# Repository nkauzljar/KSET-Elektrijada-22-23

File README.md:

# KSET-Elektrijada-22-23
KiCad project for KSET Elektrijada 2022/2023

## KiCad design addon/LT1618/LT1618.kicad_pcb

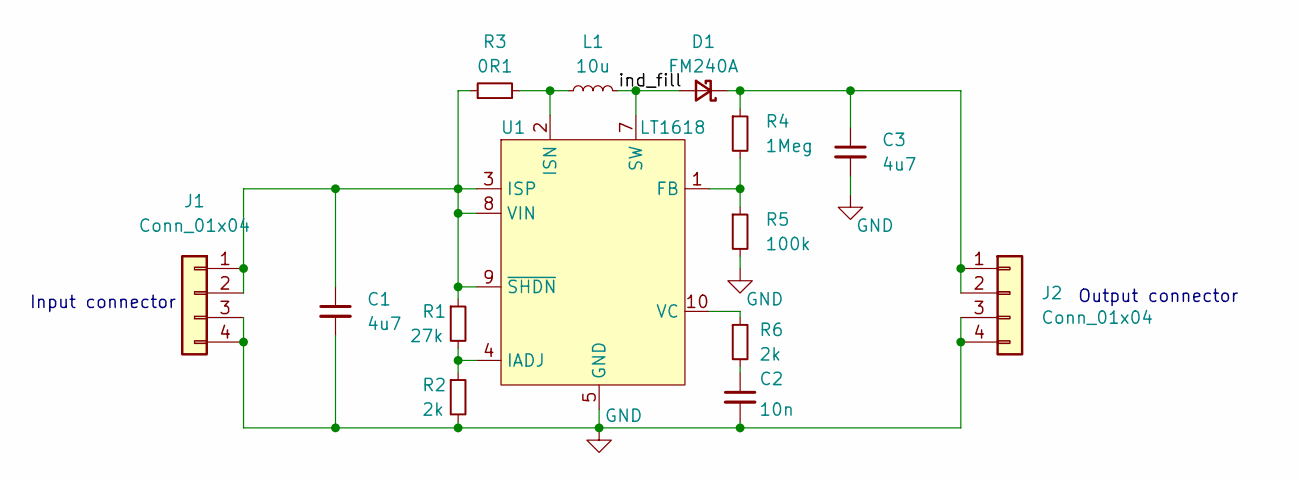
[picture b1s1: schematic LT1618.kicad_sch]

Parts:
C1, C3: 4u7; R_0805_2012Metric_Pad1.20x1.40mm_HandSolder
C2: 10n; R_0805_2012Metric_Pad1.20x1.40mm_HandSolder
D1: FM240A; D_SMB_Handsoldering
J1, J2: Conn_01x04; PinHeader_1x04_P2.54mm_Vertical
L1: 10u; L_Bourns_SRN6045TA
R1: 27k; R_0805_2012Metric_Pad1.20x1.40mm_HandSolder
R2, R6: 2k; R_0805_2012Metric_Pad1.20x1.40mm_HandSolder
R3: 0R1; R_0805_2012Metric_Pad1.20x1.40mm_HandSolder
R4: 1Meg; R_0805_2012Metric_Pad1.20x1.40mm_HandSolder
R5: 100k; R_0805_2012Metric_Pad1.20x1.40mm_HandSolder
U1: LT1618; MSOP-10_3x3mm_P0.5mm

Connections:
/ind_fill: D1.2 (A), L1.2, U1.7 (SW)
GND: C1.2, C2.2, C3.2, J1.3, J1.4, J2.3, J2.4, R2.2, R5.2, U1.5 (GND)
unnamed: C1.1, J1.1, J1.2, R1.1, R3.1, U1.3 (ISP), U1.8 (VIN), U1.9 (~SHDN)
unnamed: C2.1, R6.2
unnamed: C3.1, D1.1 (K), J2.1, J2.2, R4.1
unnamed: L1.1, R3.2, U1.2 (ISN)
unnamed: R1.2, R2.1, U1.4 (IADJ)
unnamed: R4.2, R5.1, U1.1 (FB)
unnamed: R6.1, U1.10 (VC)

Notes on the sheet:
Input connector
Output connector

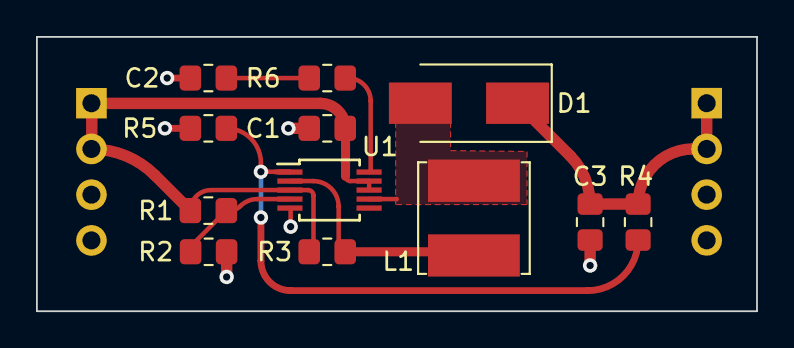
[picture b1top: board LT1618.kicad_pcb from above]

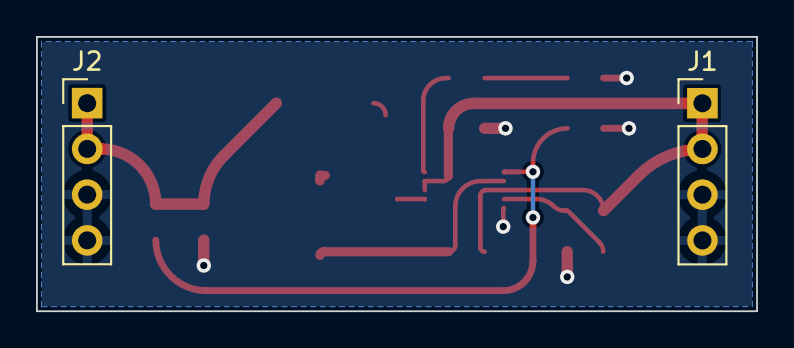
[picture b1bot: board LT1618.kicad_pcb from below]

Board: 2 copper layers, 40.0 x 15.2 mm, 14 parts (2 on the bottom side), 9 nets.

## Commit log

2022-12-20 Fix: removed PCM2903CBD.kicad_mod file
2022-12-21 Chore: added lib folder with PCM2903C symbol
2022-12-21 Chore: added LT1618 symbol and changed buck boost design
2022-12-21 Fix: fixed symbol lib table
2022-12-21 Chore: reorganised directories
2022-12-21 Chore: added LT1618 addon board project
2022-12-21 Fix: changed LT1618 addon name
2023-01-04 Updated schematics
2023-01-04 Fix: exported new schematic
2023-01-04 Chore: routed LT1618 addon board
2023-01-04 Chore: USB interface schematic
2023-01-04 Chore: USB interface design
2023-01-08 Fix: deleted unnecessary folders
2023-01-08 Chore: USB interface
2023-01-31 Fix: changed out inductor and flipped pin headers
